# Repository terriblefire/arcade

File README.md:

# Arcade

Repro Arcade Components

This repo has arcade components that I've reproduced in eagle/kicad from publically available schematics or designed myself from scratch. They come with no support or guarantees and are released as public domain.

Usually these are things i've reproduced while repairing a board. The idea is for people to be able to repair their arcade machines cheaply. 

## Seibu HB-41

Taken from Gurudumps schematic (Taken from https://gurudumps.otenko.com/re/ ) but as there was no gerbers or shop to buy the board I spent an hour producing a board layout for me (all the components have the same labels) and designed the board to be preassembled on one side by JLCPCB. 

## TC0060DCA - Digitally Controlled Attenuator for Taito. 

Fresh design of the TC0060DCA. Only tested with opwolf so far. No documentation on what V_B is in the pinout so it is NC.

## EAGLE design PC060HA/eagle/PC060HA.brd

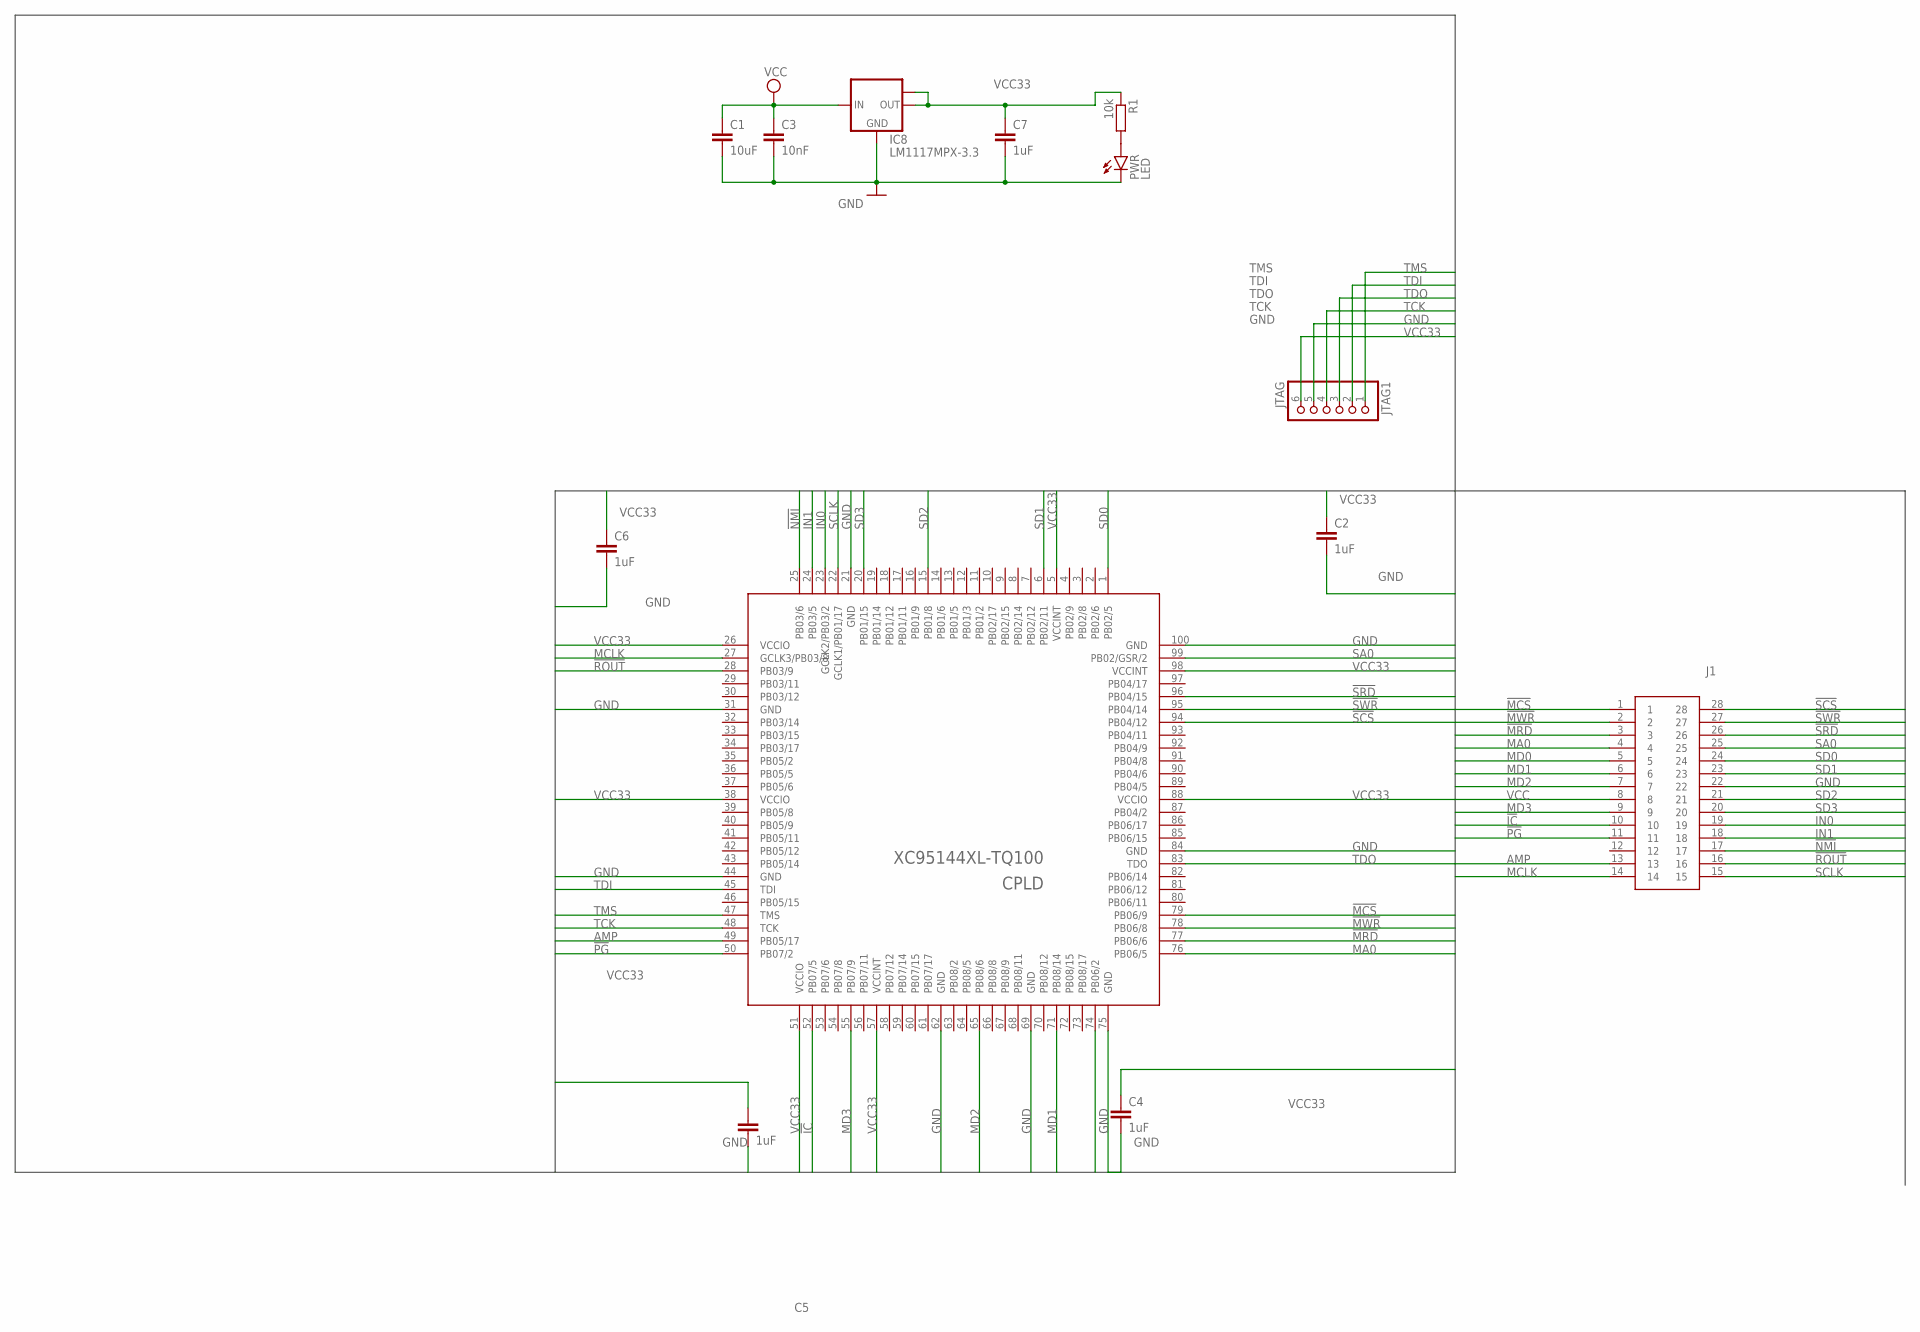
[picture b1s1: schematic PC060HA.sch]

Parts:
C1: 10uF; C1206
C2, C4, C5, C6: 1uF; C0603
C3: 10nF; C0603
C7: 1uF; C1206
CPLD: XC95144XL-TQ100; TQFP100
IC8: LM1117MPX-3.3; SOT223
J1: 150-10-628-00-106161; 1501062800106161
JTAG1: JTAG; 1X06_ROUND
PWR: LED; SML0805
R1: 10k; R0603

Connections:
!IC: CPLD.52 (PB07/5), J1.10
!MCS: CPLD.79 (PB06/9), J1.1
!MRD: CPLD.77 (PB06/6), J1.3
!MWR: CPLD.78 (PB06/8), J1.2
!NMI: CPLD.25 (PB03/6), J1.17
!PG: CPLD.50 (PB07/2), J1.11
!ROUT: CPLD.28 (PB03/9), J1.16
!SCS: CPLD.94 (PB04/12), J1.28
!SRD: CPLD.96 (PB04/15), J1.26
!SWR: CPLD.95 (PB04/14), J1.27
AMP: CPLD.49 (PB05/17), J1.13
GND: C1.2, C2.2, C3.2, C4.2, C5.2, C6.2, C7.2, CPLD.21 (GND), CPLD.31 (GND), CPLD.44 (GND), CPLD.62 (GND), CPLD.69 (GND), CPLD.75 (GND), CPLD.84 (GND), CPLD.100 (GND), IC8.1 (GND), J1.22, JTAG1.5, PWR.C
IN0: CPLD.23 (GCLK2/PB03/2), J1.19
IN1: CPLD.24 (PB03/5), J1.18
MA0: CPLD.76 (PB06/5), J1.4
MCLK: CPLD.27 (GCLK3/PB03/8), J1.14
MD0: CPLD.74 (PB06/2), J1.5
MD1: CPLD.71 (PB08/14), J1.6
MD2: CPLD.65 (PB08/6), J1.7
MD3: CPLD.55 (PB07/9), J1.9
unnamed: PWR.A, R1.2
SA0: CPLD.99 (PB02/GSR/2), J1.25
SCLK: CPLD.22 (GCLK1/PB01/17), J1.15
SD0: CPLD.1 (PB02/5), J1.24
SD1: CPLD.6 (PB02/11), J1.23
SD2: CPLD.15 (PB01/8), J1.21
SD3: CPLD.20 (PB01/15), J1.20
TCK: CPLD.48 (TCK), JTAG1.4
TDI: CPLD.45 (TDI), JTAG1.2
TDO: CPLD.83 (TDO), JTAG1.3
TMS: CPLD.47 (TMS), JTAG1.1
VCC: C1.1, C3.1, IC8.3 (IN), J1.8
VCC33: C2.1, C4.1, C5.1, C6.1, C7.1, CPLD.5 (VCCINT), CPLD.26 (VCCIO), CPLD.38 (VCCIO), CPLD.51 (VCCIO), CPLD.57 (VCCINT), CPLD.88 (VCCIO), CPLD.98 (VCCINT), IC8.2 (OUT), IC8.TAB (OUT1), JTAG1.6, R1.1

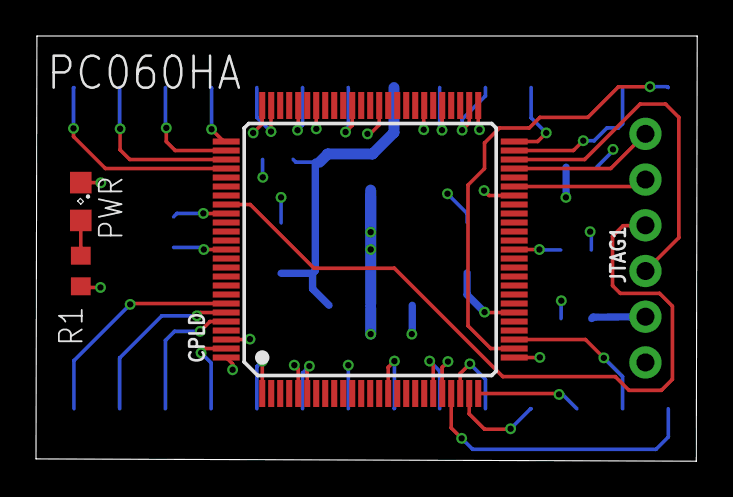
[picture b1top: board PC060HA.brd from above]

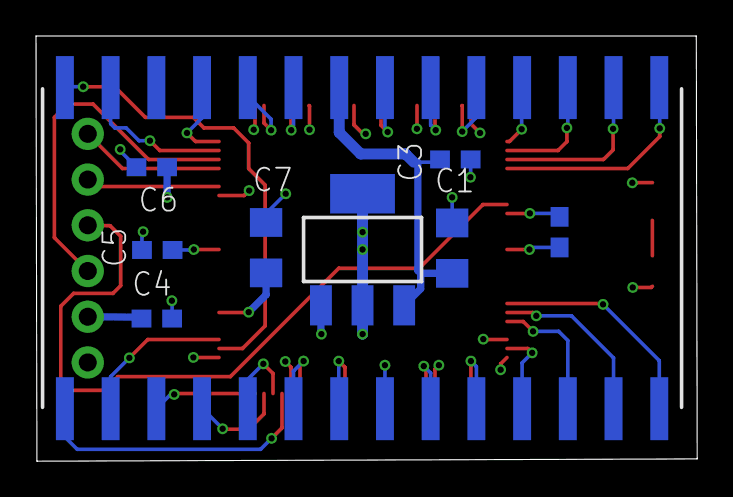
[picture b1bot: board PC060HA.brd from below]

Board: 4 copper layers, 36.7 x 23.6 mm, 13 parts (9 on the bottom side), 33 nets.

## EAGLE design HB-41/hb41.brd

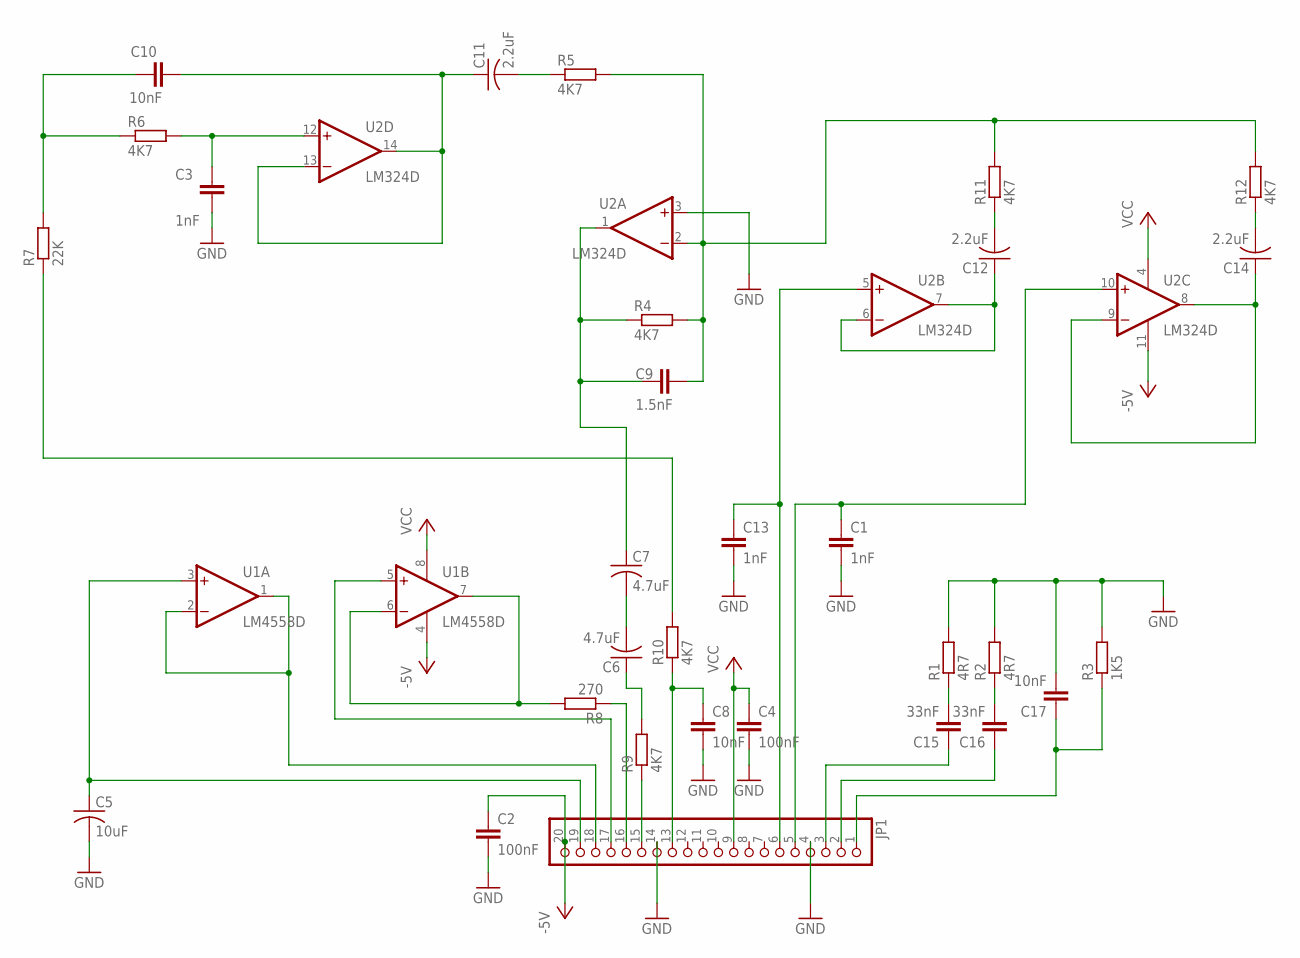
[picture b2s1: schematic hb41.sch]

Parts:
C1, C13: 1nF; C0805K
C2: 100nF; C0805K
C3: 1nF; C0603
C4: 100nF; C0603
C5: 10uF; C1206K
C6, C7: 4.7uF; C1206K
C8, C17: 10nF; C0603
C9: 1.5nF; C0805K
C10: 10nF; C0805K
C11, C12, C14: 2.2uF; C1206K
C15, C16: 33nF; C0603
JP1: PINHD-1X20-BIG; 1X20-BIG
R1, R2: 4R7; R0603
R3: 1K5; R0603
R4, R5, R6, R9, R10, R11, R12: 4K7; R0603
R7: 22K; R0603
R8: 270; R0603
U1: LM4558D; SO08
U2: LM324D; SO14

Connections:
-5V: C2.1, JP1.20, U1.4 (V-), U2.11 (V-)
GND: C1.2, C2.2, C3.1, C4.2, C5.2, C8.2, C13.2, C17.2, JP1.4, JP1.14, R1.2, R2.2, R3.2, U2.3 (+IN)
unnamed: C1.1, JP1.5, U2.10 (+IN)
unnamed: C14.1, U2.8 (OUT), U2.9 (-IN)
unnamed: C12.1, U2.6 (-IN), U2.7 (OUT)
unnamed: C13.1, JP1.6, U2.5 (+IN)
unnamed: C15.2, R1.1
unnamed: C16.2, R2.1
unnamed: C17.1, JP1.1, R3.1
unnamed: C12.2, R11.1
unnamed: C16.1, JP1.2
unnamed: C15.1, JP1.3
unnamed: C14.2, R12.1
unnamed: C8.1, JP1.13, R10.1
unnamed: C9.2, R4.2, R5.2, R11.2, R12.2, U2.2 (-IN)
unnamed: R7.1, R10.2
unnamed: C10.1, R6.1, R7.2
unnamed: C3.2, R6.2, U2.12 (+IN)
unnamed: C10.2, C11.1, U2.13 (-IN), U2.14 (OUT)
unnamed: C7.1, C9.1, R4.1, U2.1 (OUT)
unnamed: C11.2, R5.1
unnamed: C6.2, C7.2
unnamed: C6.1, R9.2
unnamed: JP1.15, R9.1
unnamed: JP1.16, R8.1
unnamed: R8.2, U1.6 (-IN), U1.7 (OUT)
unnamed: JP1.17, U1.5 (+IN)
unnamed: C5.1, JP1.19, U1.3 (+IN)
unnamed: JP1.18, U1.1 (OUT), U1.2 (-IN)
VCC: C4.1, JP1.9, U1.8 (V+), U2.4 (V+)

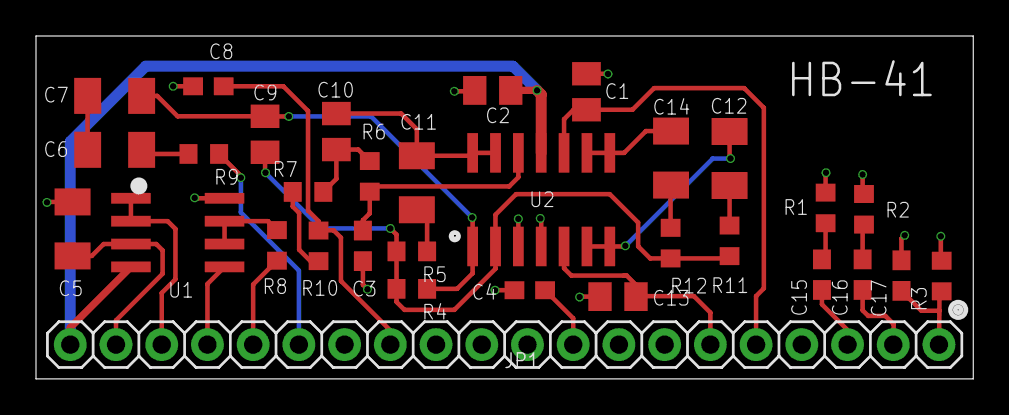
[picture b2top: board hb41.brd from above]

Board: 4 copper layers, 52.1 x 19.1 mm, 32 parts (0 on the bottom side), 30 nets.

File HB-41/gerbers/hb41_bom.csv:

Comment,Designator,Footprint,LCSC Part #
,JP1,1X20-BIG,
1.5nF,C9,C0805K,
1K5,R3,R0603,
1nF,C3,C0603,
1nF,C1 C13,C0805K,
2.2uF,C11 C12 C14,C1206K,
4.7uF,C6 C7,C1206K,
4K7,R4 R5 R6 R9 R10 R11 R12,R0603,
4R7,R1 R2,R0603,
10nF,C8 C17,C0603,
10nF,C10,C0805K,
10uF,C5,C1206K,
22K,R7,R0603,
33nF,C15 C16,C0603,
100nF,C4,C0603,
100nF,C2,C0805K,
270,R8,R0603,
LM324D,U2,SO14,
LM4558D,U1,SO08,

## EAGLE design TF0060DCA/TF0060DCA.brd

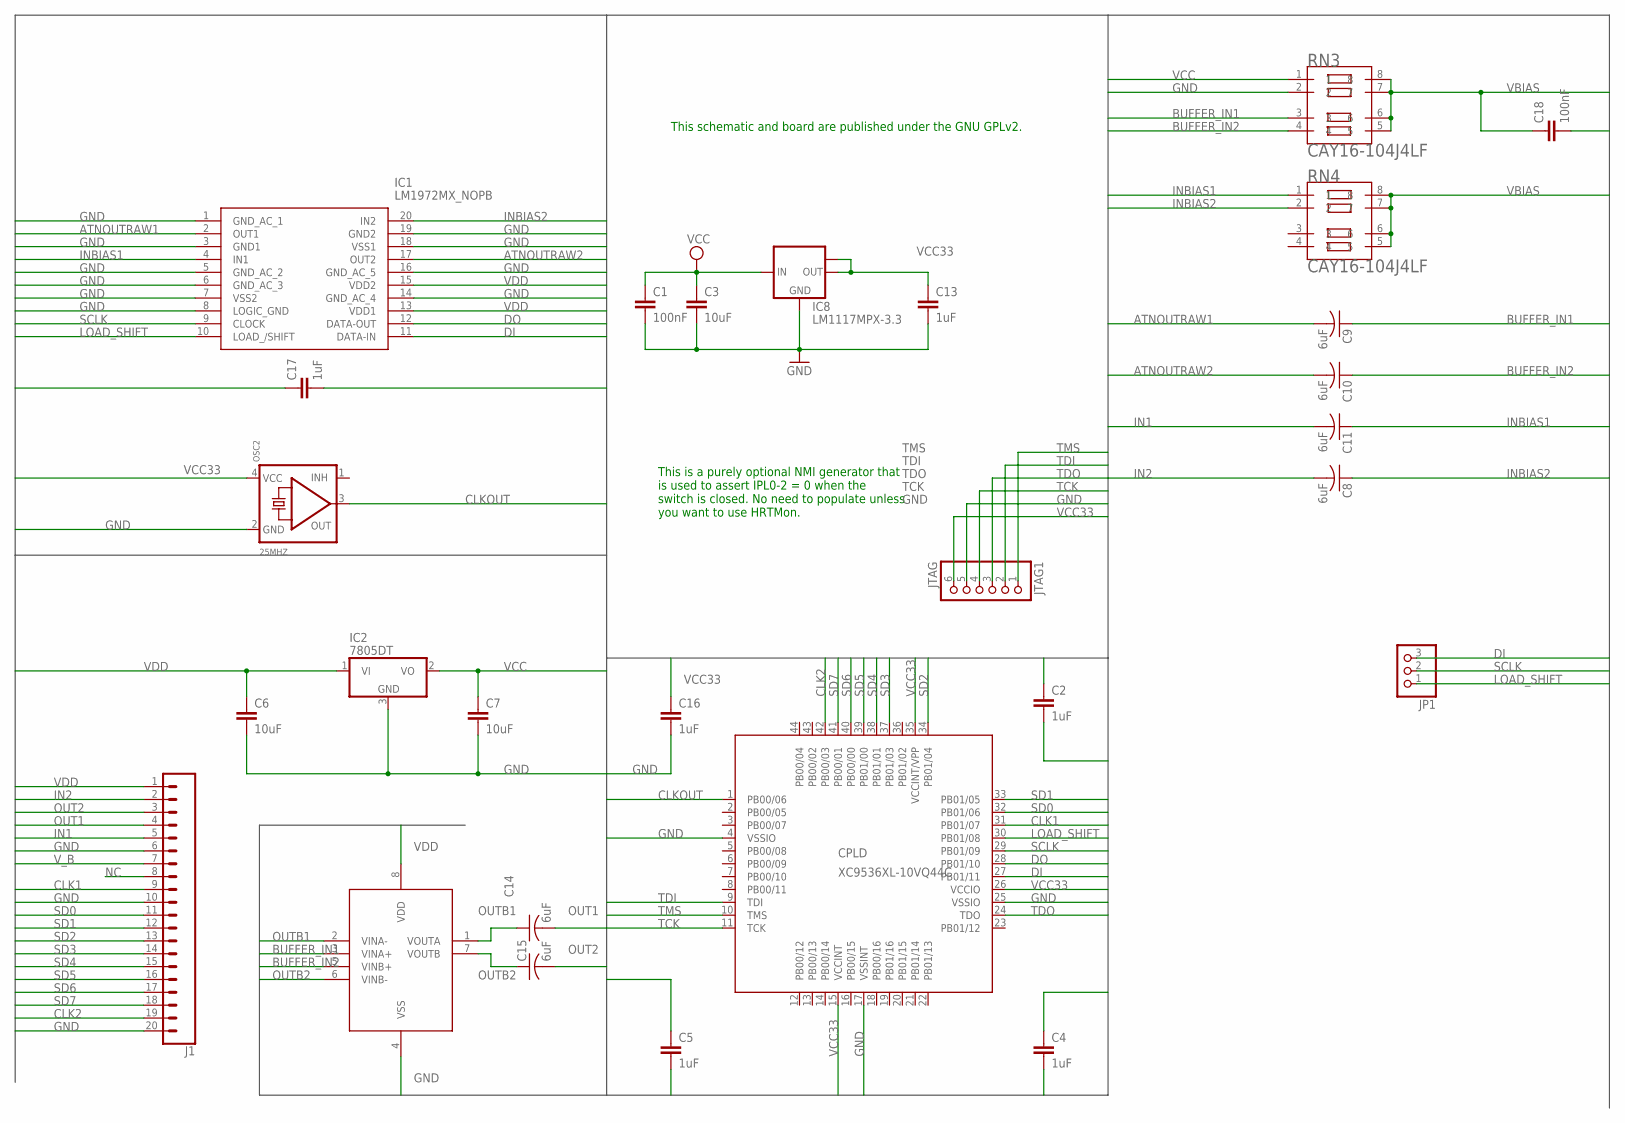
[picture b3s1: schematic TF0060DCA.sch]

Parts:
C1: 100nF; C1206
C2, C4, C5, C16, C17: 1uF; C0603
C3: 10uF; C0603
C6, C7: 10uF; C1206
C8, C9, C10, C11, C14, C15: 6uF; C0805
C13: 1uF; C1206
C18: 100nF; C0603
CPLD: XC9536XL-10VQ44C; SQFP-S-10X10-44
IC1: LM1972MX_NOPB; SOIC127P1030X265-20N
IC2: 7805DT; TO252
IC8: LM1117MPX-3.3; SOT223
IC12: MCP6002T-I_SN; SOIC127P600X175-8N
J1: CONN_20; 1X20
JP1: PINHD-1X3; 1X03
JTAG1: JTAG; 1X06_ROUND
OSC2: 25MHZ; OSC_7X5MM
RN3, RN4: CAY16-104J4LF; RESCAXE80P320X160-8N

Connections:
ATNOUTRAW1: C9.2, IC1.2 (OUT1)
ATNOUTRAW2: C10.2, IC1.17 (OUT2)
BUFFER_IN1: C9.1, IC12.3 (VINA+), RN3.3
BUFFER_IN2: C10.1, IC12.5 (VINB+), RN3.4
CLK1: CPLD.31 (PB01/07), J1.9
CLK2: CPLD.42 (PB00/03), J1.19
CLKOUT: CPLD.1 (PB00/06), OSC2.3 (OUT)
DI: CPLD.27 (PB01/11), IC1.11 (DATA-IN), JP1.3
DO: CPLD.28 (PB01/10), IC1.12 (DATA-OUT)
GND: C1.2, C2.2, C3.2, C4.2, C5.2, C6.2, C7.2, C13.2, C16.2, C17.2, C18.2, CPLD.4 (VSSIO), CPLD.17 (VSSINT), CPLD.25 (VSSIO), IC1.1 (GND_AC_1), IC1.3 (GND1), IC1.5 (GND_AC_2), IC1.6 (GND_AC_3), IC1.7 (VSS2), IC1.8 (LOGIC_GND), IC1.14 (GND_AC_4), IC1.16 (GND_AC_5), IC1.18 (VSS1), IC1.19 (GND2), IC2.3 (GND), IC8.1 (GND), IC12.4 (VSS), J1.6, J1.10, J1.20, JTAG1.5, OSC2.2 (GND), RN3.2
IN1: C11.2, J1.5
IN2: C8.2, J1.2
INBIAS1: C11.1, IC1.4 (IN1), RN4.1
INBIAS2: C8.1, IC1.20 (IN2), RN4.2
LOAD_SHIFT: CPLD.30 (PB01/08), IC1.10 (LOAD_/SHIFT), JP1.1
NC: J1.8
OUT1: C14.2, J1.4
OUT2: C15.2, J1.3
OUTB1: C14.1, IC12.1 (VOUTA), IC12.2 (VINA-)
OUTB2: C15.1, IC12.6 (VINB-), IC12.7 (VOUTB)
SCLK: CPLD.29 (PB01/09), IC1.9 (CLOCK), JP1.2
SD0: CPLD.32 (PB01/06), J1.11
SD1: CPLD.33 (PB01/05), J1.12
SD2: CPLD.34 (PB01/04), J1.13
SD3: CPLD.37 (PB01/03), J1.14
SD4: CPLD.38 (PB01/01), J1.15
SD5: CPLD.39 (PB01/00), J1.16
SD6: CPLD.40 (PB00/00), J1.17
SD7: CPLD.41 (PB00/01), J1.18
TCK: CPLD.11 (TCK), JTAG1.4
TDI: CPLD.9 (TDI), JTAG1.2
TDO: CPLD.24 (TDO), JTAG1.3
TMS: CPLD.10 (TMS), JTAG1.1
VBIAS: C18.1, RN3.5, RN3.6, RN3.7, RN3.8, RN4.5, RN4.6, RN4.7, RN4.8
VCC: C1.1, C3.1, C7.1, C17.1, IC2.2 (VO), IC8.3 (IN), RN3.1
VCC33: C2.1, C4.1, C5.1, C13.1, C16.1, CPLD.15 (VCCINT), CPLD.26 (VCCIO), CPLD.35 (VCCINT/VPP), IC8.2 (OUT), IC8.TAB (OUT1), JTAG1.6, OSC2.4 (VCC)
VDD: C6.1, IC1.13 (VDD1), IC1.15 (VDD2), IC2.1 (VI), IC12.8 (VDD), J1.1
V_B: J1.7

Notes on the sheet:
This is a purely optional NMI generator that is used to assert IPL0-2 = 0 when the switch is closed. No need to populate unless you want to use HRTMon.
This schematic and board are published under the GNU GPLv2.

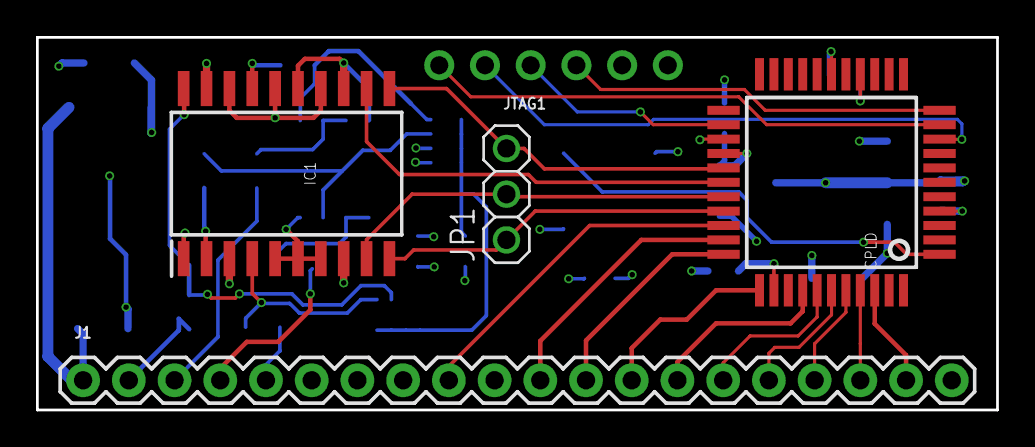
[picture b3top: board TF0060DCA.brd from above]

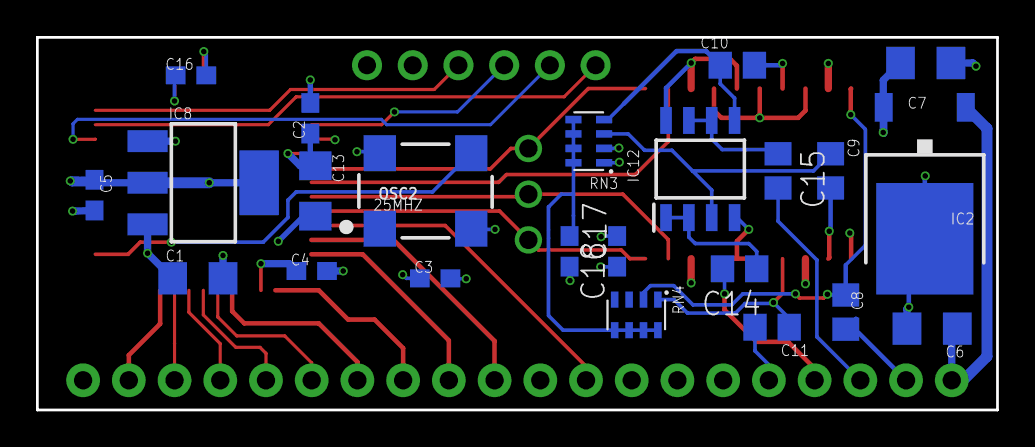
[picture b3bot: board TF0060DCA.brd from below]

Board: 4 copper layers, 53.3 x 20.7 mm, 28 parts (23 on the bottom side), 36 nets.

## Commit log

2025-01-02 HB-41 check in
2025-01-03 0060DCA board checkin. Untested board
2025-01-12 upgraded the DC bias
2025-01-12 basic working version of the firmware
2025-01-24 calibrated
2025-01-26 Updated to CH32 control chip
2025-02-15 CH32 revision of the board
2025-02-17 ok first untested version of PC060HA. Ugly physical form
2025-02-18 shrunk down to small board with SMD DiL
2025-02-22 fixing makefile for docker inline builds
2025-02-22 buid files added
2025-02-22 updating makefiles
2025-02-22 updating actions
2025-02-22 cleanup improved
2025-02-22 stupid git
2025-02-22 missed a makefile
2025-02-23 workflow fix
2025-02-23 archive artifacts
2025-02-23 artifacts

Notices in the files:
parts and their libraries:
microbuilder: This work is placed in the public domain, and may be freely used for commercial and non-commercial work with the following conditions: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
SparkFun-Connectors: Licensing: Creative Commons ShareAlike 4.0 International - https://creativecommons.org/licenses/by-sa/4.0
